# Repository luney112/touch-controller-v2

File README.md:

# touch-controller-v2

Version 2 of my touch controller for chunithm.

## TODO

- [ ] Finish firmware
- [ ] Test fully
- [ ] Write out docs and assembly instructions

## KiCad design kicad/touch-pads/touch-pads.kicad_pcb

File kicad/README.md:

# PCBs

There are two different PCB types: `mainboard` and `touch-pads`.

### mainboard

- Primary board everything connects to
- Only 1 copy of the board is required

### touch-pads

- Has the touch pads and LEDs
- 4 copies of the board is required

### development

- Use KiCad 9+
- Install the [espressif libraries](https://github.com/espressif/kicad-libraries)
- Install interactive html bom plugin

### manufacturing

- The `gerber.zip` files that are committed should be enough for manufacturing
- I use JlcPcb as they seem to offer the best prices for boards larger than 100mm x 100mm
- Suggested settings:
  - FR-4
  - 2 layers
  - At least 4 boards
  - 1.6mm thickness
  - Black color
  - HASL finish
  - 1 oz cu
  - Tented vias
  - 0.3mm min via hole size
  - Remove mark on PCB

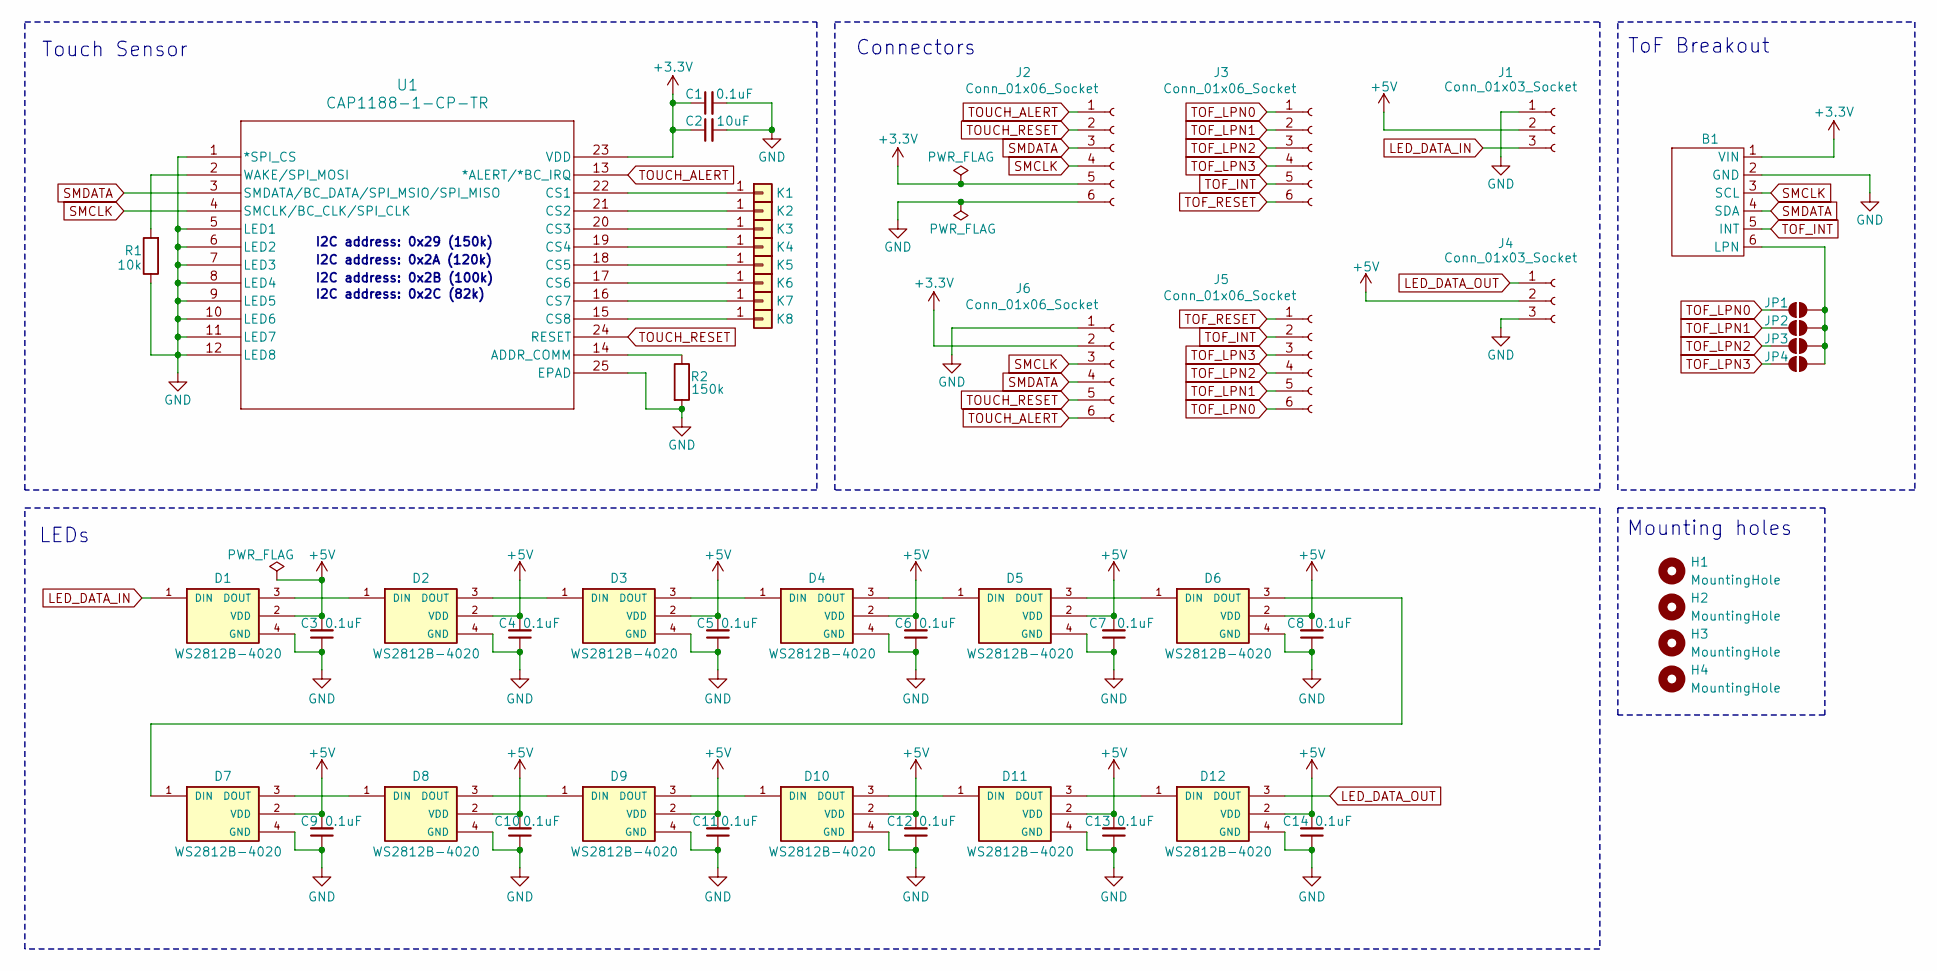
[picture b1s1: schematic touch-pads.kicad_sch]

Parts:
B1: VL53L5CX_Breakout_Aliexpress
C1, C3, C4, C5, C6, C7, C8, C9, C10, C11, C12, C13, C14: 0.1uF; C_0805_2012Metric_Pad1.18x1.45mm_HandSolder
C2: 10uF; C_0805_2012Metric_Pad1.18x1.45mm_HandSolder
D1, D2, D3, D4, D5, D6, D7, D8, D9, D10, D11, D12: WS2812B-4020; LED_WS2812B-4020; PARTREV V1.2
H1, H2, H3, H4: MountingHole; MountingHole_3.2mm_M3
J1, J4: Conn_01x03_Socket; JST_PH_S3B-PH-SM4-TB_1x03-1MP_P2.00mm_Horizontal
J2, J3, J5, J6: Conn_01x06_Socket; JST_GH_SM06B-GHS-TB_1x06-1MP_P1.25mm_Horizontal
JP1, JP2, JP3, JP4: SolderJumper_2_Open; SolderJumper-2_P1.3mm_Open_RoundedPad1.0x1.5mm
K1, K2, K3, K4, K5, K6, K7, K8: Conn_01x01; TouchKey_Standard
R1: 10k; R_0805_2012Metric_Pad1.20x1.40mm_HandSolder
R2: 150k; R_0805_2012Metric_Pad1.20x1.40mm_HandSolder
U1: CAP1188-1-CP-TR; QFN24_4X4MC_MCH

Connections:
+3.3V: B1.1 (VIN), C1.1, C2.1, J2.5, J6.2, U1.23 (VDD)
+5V: C3.2, C4.2, C5.2, C6.2, C7.2, C8.2, C9.2, C10.2, C11.2, C12.2, C13.2, C14.2, D1.2 (VDD), D2.2 (VDD), D3.2 (VDD), D4.2 (VDD), D5.2 (VDD), D6.2 (VDD), D7.2 (VDD), D8.2 (VDD), D9.2 (VDD), D10.2 (VDD), D11.2 (VDD), D12.2 (VDD), J1.2, J4.2
GND: B1.2 (GND), C1.2, C2.2, C3.1, C4.1, C5.1, C6.1, C7.1, C8.1, C9.1, C10.1, C11.1, C12.1, C13.1, C14.1, D1.4 (GND), D2.4 (GND), D3.4 (GND), D4.4 (GND), D5.4 (GND), D6.4 (GND), D7.4 (GND), D8.4 (GND), D9.4 (GND), D10.4 (GND), D11.4 (GND), D12.4 (GND), J1.1, J2.6, J4.3, J6.1, R1.1, R2.2, U1.1 (*SPI_CS), U1.5 (LED1), U1.6 (LED2), U1.7 (LED3), U1.8 (LED4), U1.9 (LED5), U1.10 (LED6), U1.11 (LED7), U1.12 (LED8), U1.25 (EPAD)
LED_DATA_IN: D1.1 (DIN), J1.3
LED_DATA_OUT: D12.3 (DOUT), J4.1
unnamed: B1.6 (LPN), JP1.2 (B), JP2.2 (B), JP3.2 (B), JP4.2 (B)
unnamed: D1.3 (DOUT), D2.1 (DIN)
unnamed: D2.3 (DOUT), D3.1 (DIN)
unnamed: D3.3 (DOUT), D4.1 (DIN)
unnamed: D4.3 (DOUT), D5.1 (DIN)
unnamed: D5.3 (DOUT), D6.1 (DIN)
unnamed: D6.3 (DOUT), D7.1 (DIN)
unnamed: D7.3 (DOUT), D8.1 (DIN)
unnamed: D8.3 (DOUT), D9.1 (DIN)
unnamed: D9.3 (DOUT), D10.1 (DIN)
unnamed: D10.3 (DOUT), D11.1 (DIN)
unnamed: D11.3 (DOUT), D12.1 (DIN)
unnamed: K1.1, U1.22 (CS1)
unnamed: K2.1, U1.21 (CS2)
unnamed: K3.1, U1.20 (CS3)
unnamed: K4.1, U1.19 (CS4)
unnamed: K5.1, U1.18 (CS5)
unnamed: K6.1, U1.17 (CS6)
unnamed: K7.1, U1.16 (CS7)
unnamed: K8.1, U1.15 (CS8)
unnamed: R2.1, U1.14 (ADDR_COMM)
unnamed: R1.2, U1.2 (WAKE/SPI_MOSI)
SMCLK: B1.3 (SCL), J2.4, J6.3, U1.4 (SMCLK/BC_CLK/SPI_CLK)
SMDATA: B1.4 (SDA), J2.3, J6.4, U1.3 (SMDATA/BC_DATA/SPI_MSIO/SPI_MISO)
TOF_INT: B1.5 (INT), J3.5, J5.2
TOF_LPN0: J3.1, J5.6, JP1.1 (A)
TOF_LPN1: J3.2, J5.5, JP2.1 (A)
TOF_LPN2: J3.3, J5.4, JP3.1 (A)
TOF_LPN3: J3.4, J5.3, JP4.1 (A)
TOF_RESET: J3.6, J5.1
TOUCH_ALERT: J2.1, J6.6, U1.13 (*ALERT/*BC_IRQ)
TOUCH_RESET: J2.2, J6.5, U1.24 (RESET)

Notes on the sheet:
ToF Breakout
I2C address: 0x2B (100k)
I2C address: 0x29 (150k)
LEDs
Mounting holes
Touch Sensor
Connectors
I2C address: 0x2C (82k)
I2C address: 0x2A (120k)

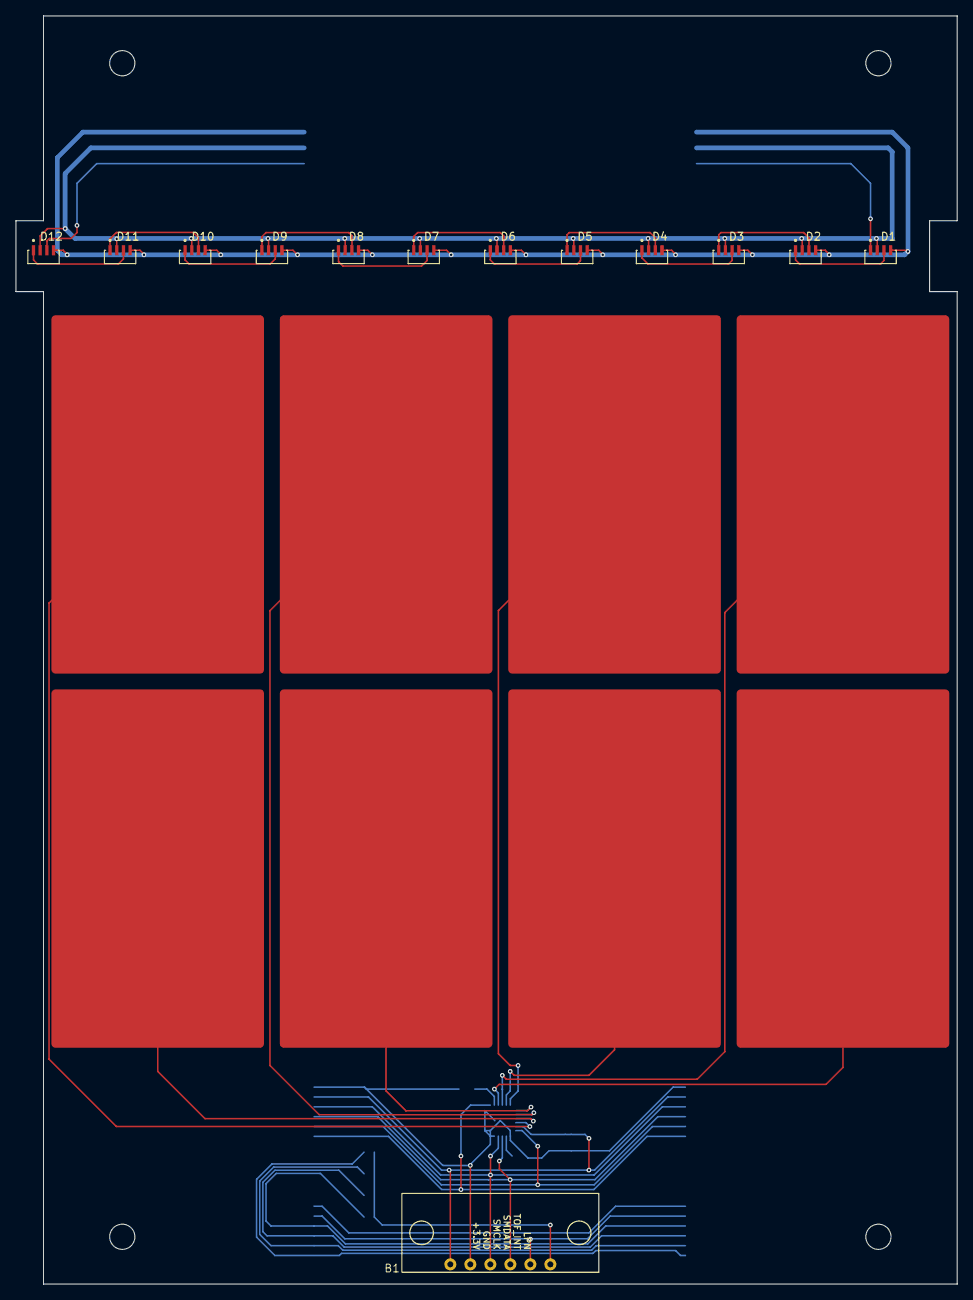
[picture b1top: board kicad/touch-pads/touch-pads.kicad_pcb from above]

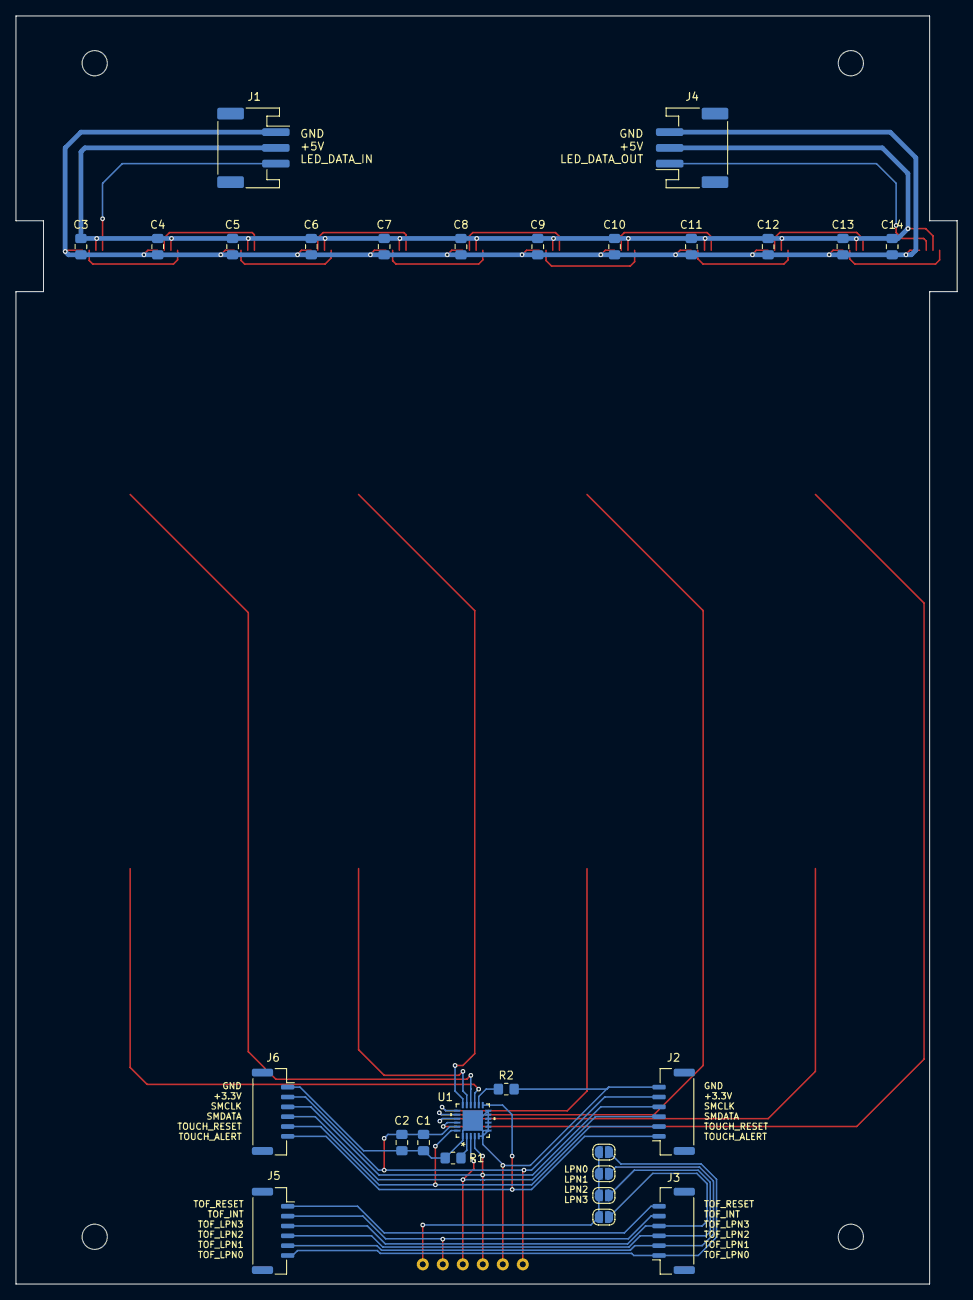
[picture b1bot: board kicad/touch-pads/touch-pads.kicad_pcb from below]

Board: 2 copper layers, 119.5 x 161.0 mm, 52 parts (27 on the bottom side), 37 nets.

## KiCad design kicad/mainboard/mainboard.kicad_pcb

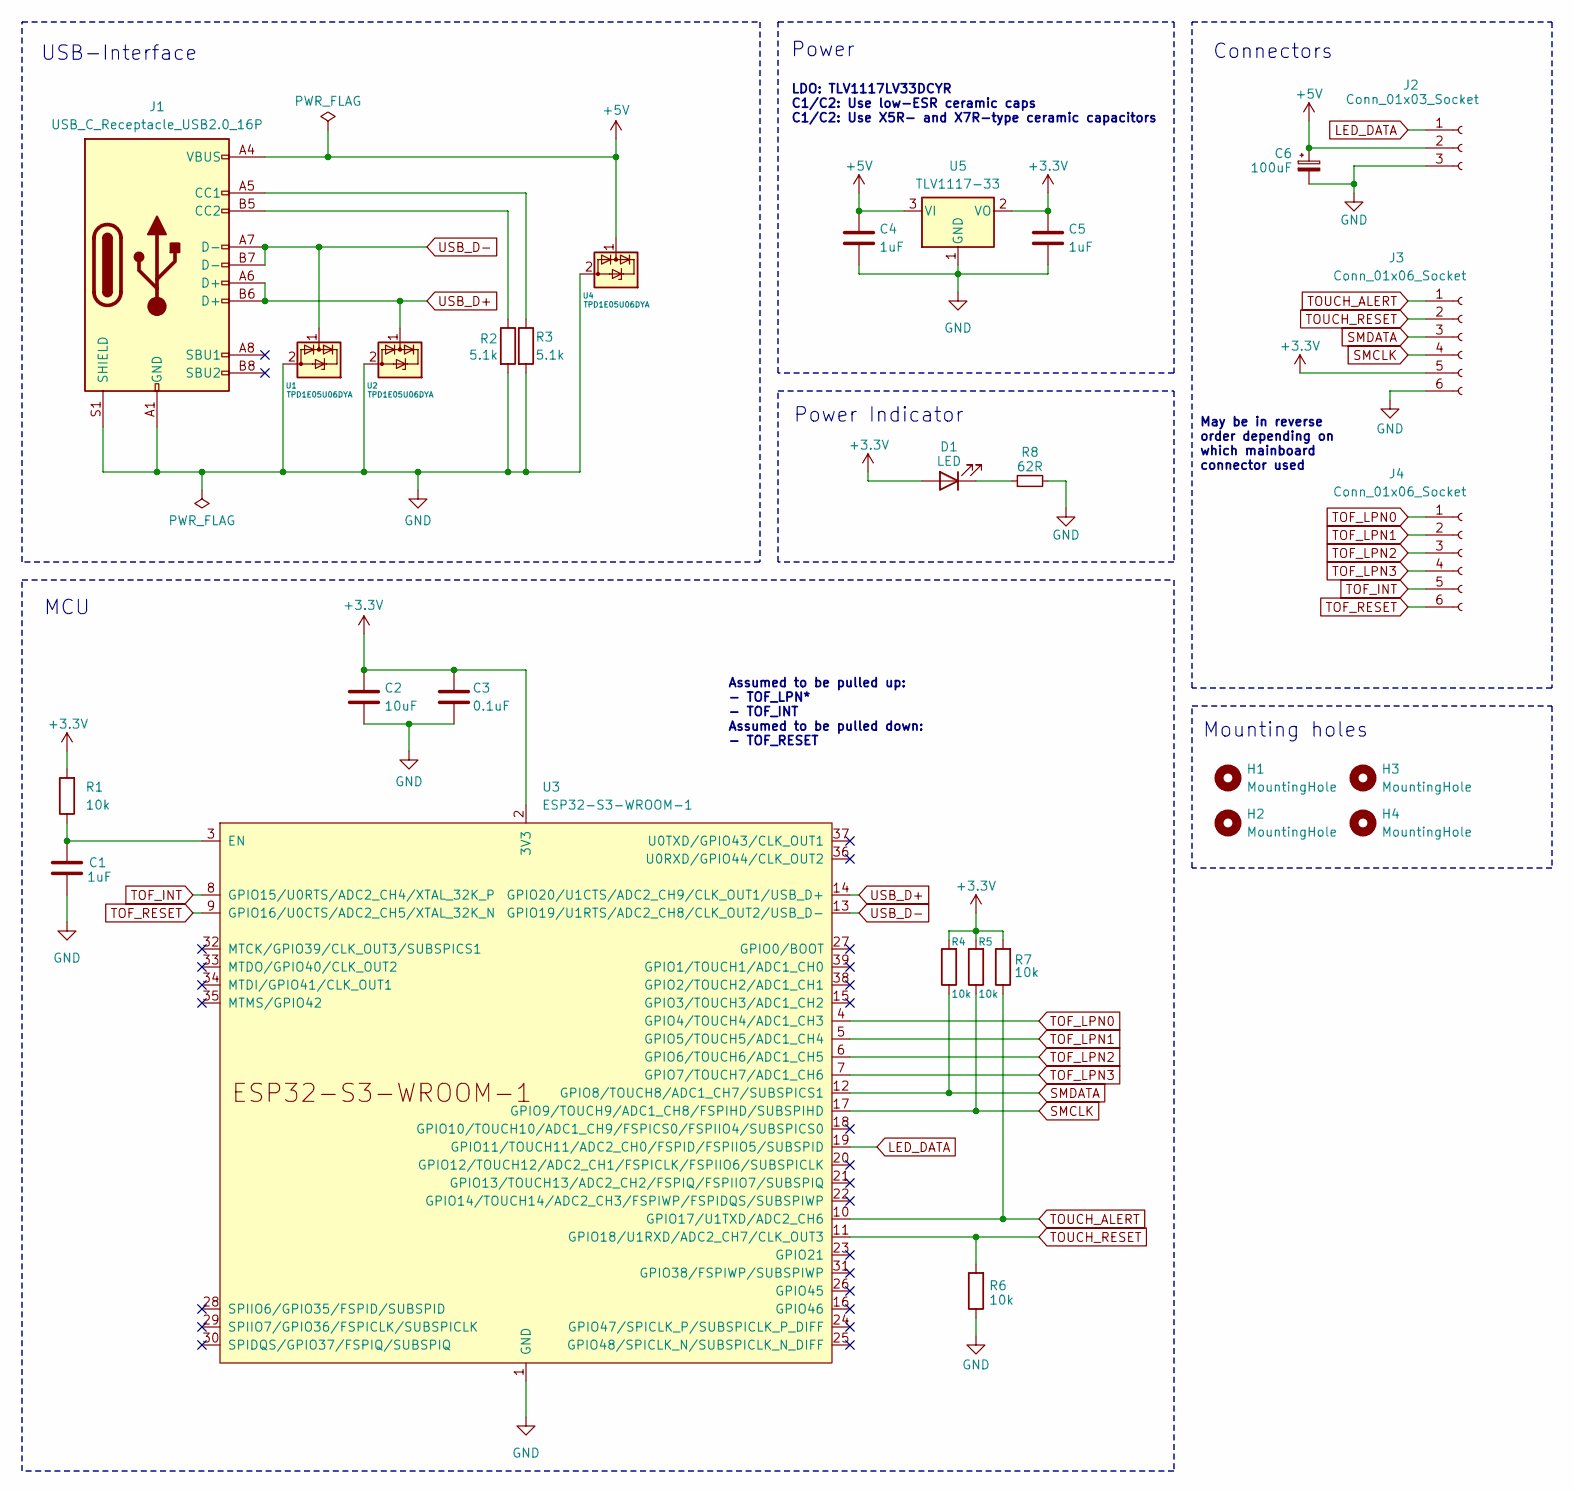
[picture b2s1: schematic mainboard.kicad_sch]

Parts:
C1, C4, C5: 1uF; C_0805_2012Metric_Pad1.18x1.45mm_HandSolder
C2: 10uF; C_0805_2012Metric_Pad1.18x1.45mm_HandSolder
C3: 0.1uF; C_0805_2012Metric_Pad1.18x1.45mm_HandSolder
C6: 100uF; CP_Elec_6.3x5.8
D1: LED; LED_0805_2012Metric_Pad1.15x1.40mm_HandSolder
H1, H2, H3, H4: MountingHole; MountingHole_2.2mm_M2
J1: USB_C_Receptacle_USB2.0_16P; USB_C_Receptacle_GCT_USB4105-xx-A_16P_TopMnt_Horizontal
J2: Conn_01x03_Socket; JST_PH_S3B-PH-SM4-TB_1x03-1MP_P2.00mm_Horizontal
J3, J4: Conn_01x06_Socket; JST_GH_SM06B-GHS-TB_1x06-1MP_P1.25mm_Horizontal
R1, R4, R5, R6, R7: 10k; R_0805_2012Metric_Pad1.20x1.40mm_HandSolder
R2, R3: 5.1k; R_0805_2012Metric_Pad1.20x1.40mm_HandSolder
R8: 62R; R_0805_2012Metric_Pad1.20x1.40mm_HandSolder
U1, U2, U4: TPD1E05U06DYA; D_SOD-523
U3: ESP32-S3-WROOM-1
U5: TLV1117-33; SOT-223-3_TabPin2

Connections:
+3.3V: C2.2, C3.2, C5.1, D1.2 (A), J3.5, R1.2, R4.2, R5.2, R7.2, U3.2 (3V3), U5.2 (VO)
+5V: C4.1, C6.1, J1.A4 (VBUS), J1.A9 (VBUS), J1.B4 (VBUS), J1.B9 (VBUS), J2.2, U4.1 (I/O), U5.3 (VI)
GND: C1.2, C2.1, C3.1, C4.2, C5.2, C6.2, J1.A1 (GND), J1.A12 (GND), J1.B1 (GND), J1.B12 (GND), J1.S1 (SHIELD), J2.3, J3.6, R2.2, R3.2, R6.1, R8.2, U1.2 (GND), U2.2 (GND), U3.1 (GND), U3.40 (GND), U3.41 (GND), U4.2 (GND), U5.1 (GND)
LED_DATA: J2.1, U3.19 (GPIO11/TOUCH11/ADC2_CH0/FSPID/FSPIIO5/S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)
unnamed: D1.1 (K), R8.1
unnamed: J1.A5 (CC1), R3.1
unnamed: J1.B5 (CC2), R2.1
unnamed: C1.1, R1.1, U3.3 (EN)
SMCLK: J3.4, R5.1, U3.17 (GPIO9/TOUCH9/ADC1_CH8/FSPIHD/SUBSPIHD)
SMDATA: J3.3, R4.1, U3.12 (GPIO8/TOUCH8/ADC1_CH7/SUBSPICS1)
TOF_INT: J4.5, U3.8 (GPIO15/U0RTS/ADC2_CH4/XTAL_32K_P)
TOF_LPN0: J4.1, U3.4 (GPIO4/TOUCH4/ADC1_CH3)
TOF_LPN1: J4.2, U3.5 (GPIO5/TOUCH5/ADC1_CH4)
TOF_LPN2: J4.3, U3.6 (GPIO6/TOUCH6/ADC1_CH5)
TOF_LPN3: J4.4, U3.7 (GPIO7/TOUCH7/ADC1_CH6)
TOF_RESET: J4.6, U3.9 (GPIO16/U0CTS/ADC2_CH5/XTAL_32K_N)
TOUCH_ALERT: J3.1, R7.1, U3.10 (GPIO17/U1TXD/ADC2_CH6)
TOUCH_RESET: J3.2, R6.2, U3.11 (GPIO18/U1RXD/ADC2_CH7/CLK_OUT3)
USB_D+: J1.A6 (D+), J1.B6 (D+), U2.1 (I/O), U3.14 (GPIO20/U1CTS/ADC2_CH9/CLK_OUT1/USB_D+)
USB_D-: J1.A7 (D-), J1.B7 (D-), U1.1 (I/O), U3.13 (GPIO19/U1RTS/ADC2_CH8/CLK_OUT2/USB_D-)

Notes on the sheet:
Assumed to be pulled up: - TOF_LPN* - TOF_INT Assumed to be pulled down: - TOF_RESET
May be in reverse order depending on which mainboard connector used
Power Indicator
Connectors
MCU
LDO: TLV1117LV33DCYR C1/C2: Use low-ESR ceramic caps C1/C2: Use X5R- and X7R-type ceramic capacitors
Mounting holes
USB-Interface
Power

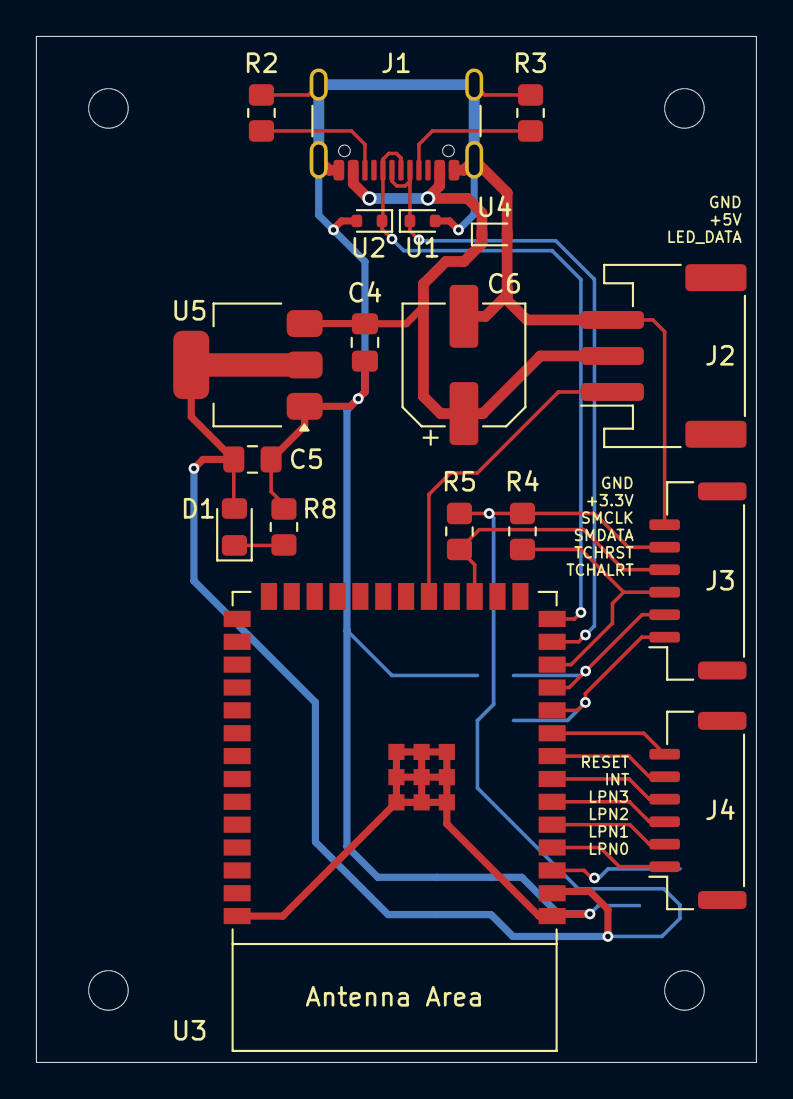
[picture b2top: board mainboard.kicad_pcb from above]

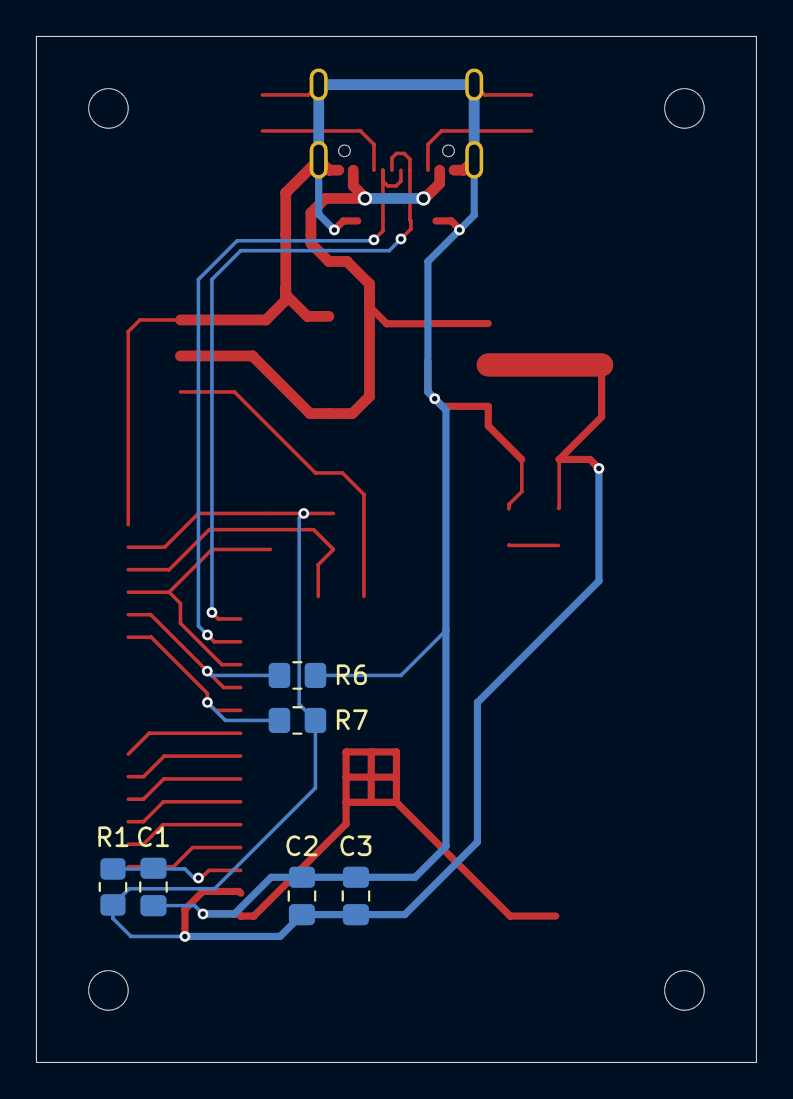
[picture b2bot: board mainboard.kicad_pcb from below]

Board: 2 copper layers, 40.0 x 57.0 mm, 28 parts (6 on the bottom side), 20 nets.

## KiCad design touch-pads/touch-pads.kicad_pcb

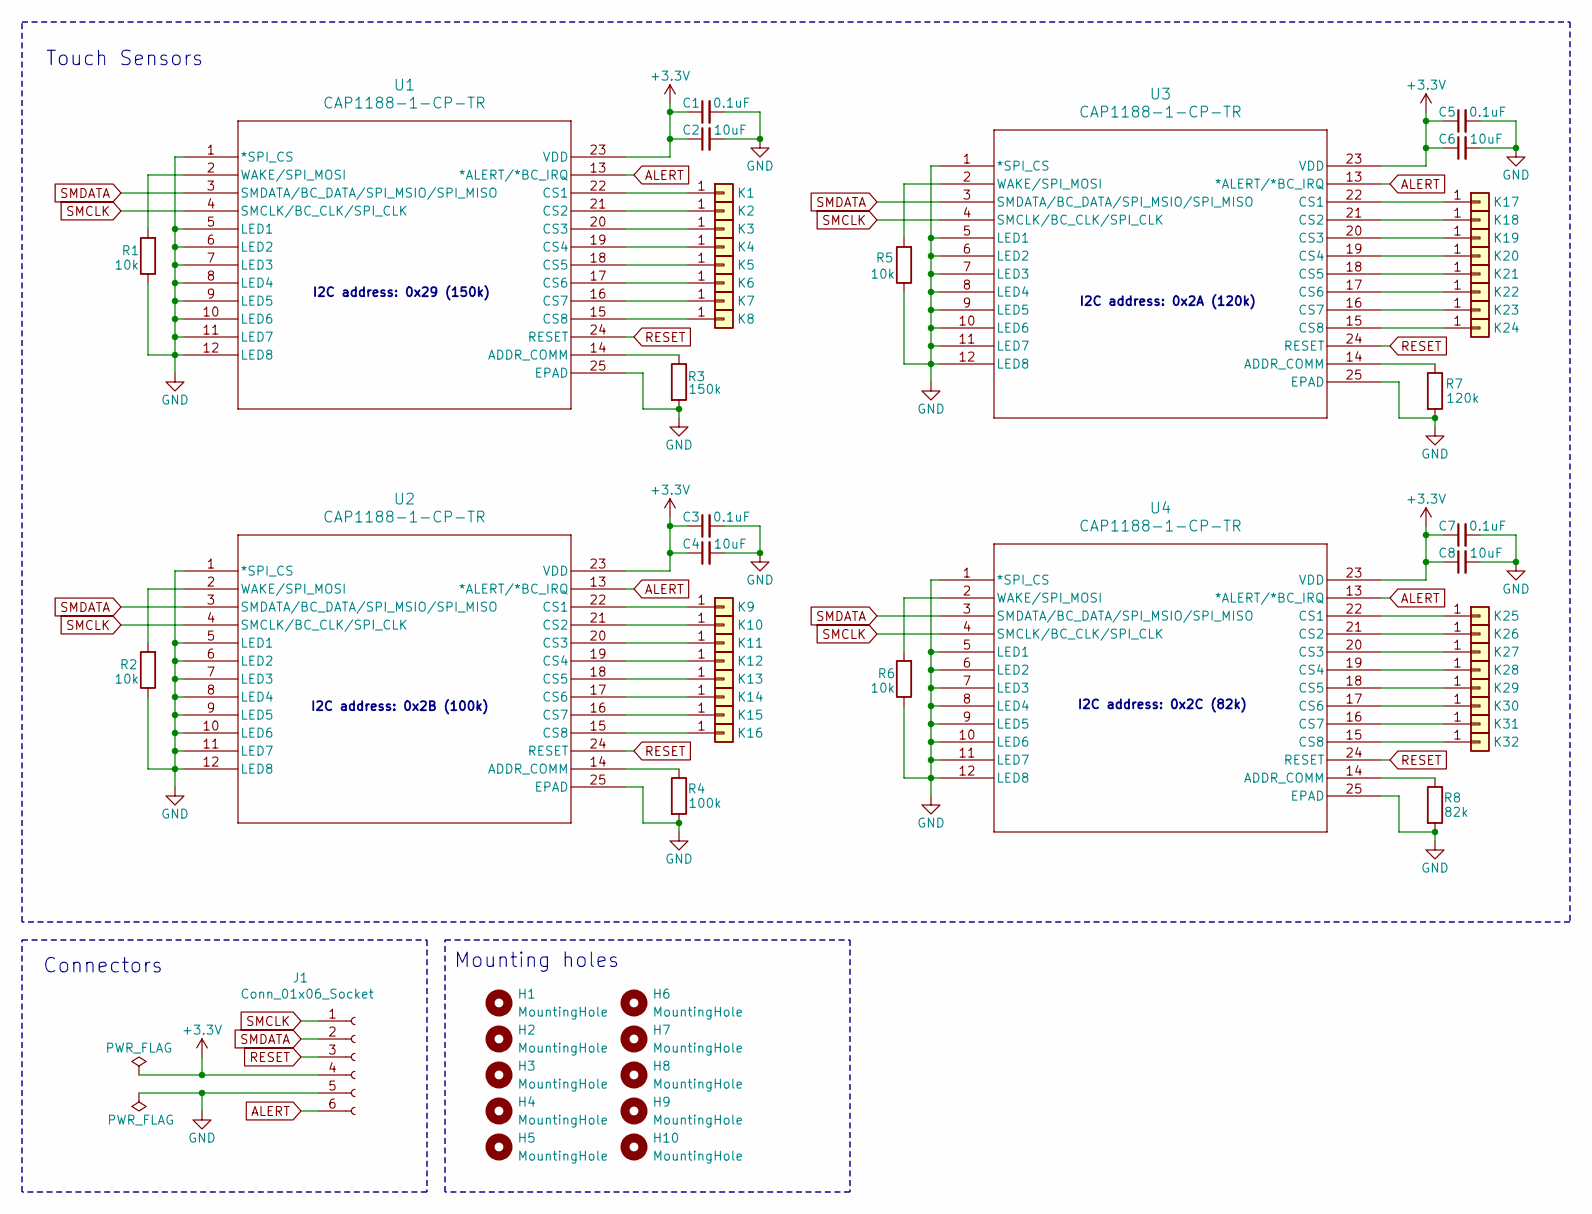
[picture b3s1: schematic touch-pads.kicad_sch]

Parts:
C1, C3, C5, C7: 0.1uF; C_0805_2012Metric_Pad1.18x1.45mm_HandSolder
C2, C4, C6, C8: 10uF; C_0805_2012Metric_Pad1.18x1.45mm_HandSolder
H1, H2, H3, H4, H5, H6, H7, H8, H9, H10: MountingHole; MountingHole_3.2mm_M3
J1: Conn_01x06_Socket; JST_XH_B6B-XH-A_1x06_P2.50mm_Vertical
K1, K2, K3, K4, K5, K6, K7, K8, K9, K10, K11, K12, K13, K14, K15, K16, K17, K18, K19, K20, K21, K22, K23, K24, K25, K26, K27, K28, K29, K30, K31, K32: Conn_01x01; TouchKey_Standard
R1, R2, R5, R6: 10k; R_0805_2012Metric_Pad1.20x1.40mm_HandSolder
R3: 150k; R_0805_2012Metric_Pad1.20x1.40mm_HandSolder
R4: 100k; R_0805_2012Metric_Pad1.20x1.40mm_HandSolder
R7: 120k; R_0805_2012Metric_Pad1.20x1.40mm_HandSolder
R8: 82k; R_0805_2012Metric_Pad1.20x1.40mm_HandSolder
U1, U2, U3, U4: CAP1188-1-CP-TR; QFN24_4X4MC_MCH

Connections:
+3.3V: C1.1, C2.1, C3.1, C4.1, C5.1, C6.1, C7.1, C8.1, J1.4, U1.23 (VDD), U2.23 (VDD), U3.23 (VDD), U4.23 (VDD)
ALERT: J1.6, U1.13 (*ALERT/*BC_IRQ), U2.13 (*ALERT/*BC_IRQ), U3.13 (*ALERT/*BC_IRQ), U4.13 (*ALERT/*BC_IRQ)
GND: C1.2, C2.2, C3.2, C4.2, C5.2, C6.2, C7.2, C8.2, J1.5, R1.1, R2.1, R3.2, R4.2, R5.1, R6.1, R7.2, R8.2, U1.1 (*SPI_CS), U1.5 (LED1), U1.6 (LED2), U1.7 (LED3), U1.8 (LED4), U1.9 (LED5), U1.10 (LED6), U1.11 (LED7), U1.12 (LED8), U1.25 (EPAD), U2.1 (*SPI_CS), U2.5 (LED1), U2.6 (LED2), U2.7 (LED3), U2.8 (LED4), U2.9 (LED5), U2.10 (LED6), U2.11 (LED7), U2.12 (LED8), U2.25 (EPAD), U3.1 (*SPI_CS), U3.5 (LED1), U3.6 (LED2), U3.7 (LED3), U3.8 (LED4), U3.9 (LED5), U3.10 (LED6), U3.11 (LED7), U3.12 (LED8), U3.25 (EPAD), U4.1 (*SPI_CS), U4.5 (LED1), U4.6 (LED2), U4.7 (LED3), U4.8 (LED4), U4.9 (LED5), U4.10 (LED6), U4.11 (LED7), U4.12 (LED8), U4.25 (EPAD)
unnamed: K1.1, U1.22 (CS1)
unnamed: K2.1, U1.21 (CS2)
unnamed: K3.1, U1.20 (CS3)
unnamed: K4.1, U1.19 (CS4)
unnamed: K5.1, U1.18 (CS5)
unnamed: K6.1, U1.17 (CS6)
unnamed: K7.1, U1.16 (CS7)
unnamed: K8.1, U1.15 (CS8)
unnamed: K9.1, U2.22 (CS1)
unnamed: K10.1, U2.21 (CS2)
unnamed: K11.1, U2.20 (CS3)
unnamed: K12.1, U2.19 (CS4)
unnamed: K13.1, U2.18 (CS5)
unnamed: K14.1, U2.17 (CS6)
unnamed: K15.1, U2.16 (CS7)
unnamed: K16.1, U2.15 (CS8)
unnamed: K17.1, U3.22 (CS1)
unnamed: K18.1, U3.21 (CS2)
unnamed: K19.1, U3.20 (CS3)
unnamed: K20.1, U3.19 (CS4)
unnamed: K21.1, U3.18 (CS5)
unnamed: K22.1, U3.17 (CS6)
unnamed: K23.1, U3.16 (CS7)
unnamed: K24.1, U3.15 (CS8)
unnamed: K25.1, U4.22 (CS1)
unnamed: K26.1, U4.21 (CS2)
unnamed: K27.1, U4.20 (CS3)
unnamed: K28.1, U4.19 (CS4)
unnamed: K29.1, U4.18 (CS5)
unnamed: K30.1, U4.17 (CS6)
unnamed: K31.1, U4.16 (CS7)
unnamed: K32.1, U4.15 (CS8)
unnamed: R3.1, U1.14 (ADDR_COMM)
unnamed: R1.2, U1.2 (WAKE/SPI_MOSI)
unnamed: R4.1, U2.14 (ADDR_COMM)
unnamed: R2.2, U2.2 (WAKE/SPI_MOSI)
unnamed: R7.1, U3.14 (ADDR_COMM)
unnamed: R5.2, U3.2 (WAKE/SPI_MOSI)
unnamed: R8.1, U4.14 (ADDR_COMM)
unnamed: R6.2, U4.2 (WAKE/SPI_MOSI)
RESET: J1.3, U1.24 (RESET), U2.24 (RESET), U3.24 (RESET), U4.24 (RESET)
SMCLK: J1.1, U1.4 (SMCLK/BC_CLK/SPI_CLK), U2.4 (SMCLK/BC_CLK/SPI_CLK), U3.4 (SMCLK/BC_CLK/SPI_CLK), U4.4 (SMCLK/BC_CLK/SPI_CLK)
SMDATA: J1.2, U1.3 (SMDATA/BC_DATA/SPI_MSIO/SPI_MISO), U2.3 (SMDATA/BC_DATA/SPI_MSIO/SPI_MISO), U3.3 (SMDATA/BC_DATA/SPI_MSIO/SPI_MISO), U4.3 (SMDATA/BC_DATA/SPI_MSIO/SPI_MISO)

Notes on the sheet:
I2C address: 0x2B (100k)
I2C address: 0x29 (150k)
Mounting holes
Touch Sensors
Connectors
I2C address: 0x2C (82k)
I2C address: 0x2A (120k)

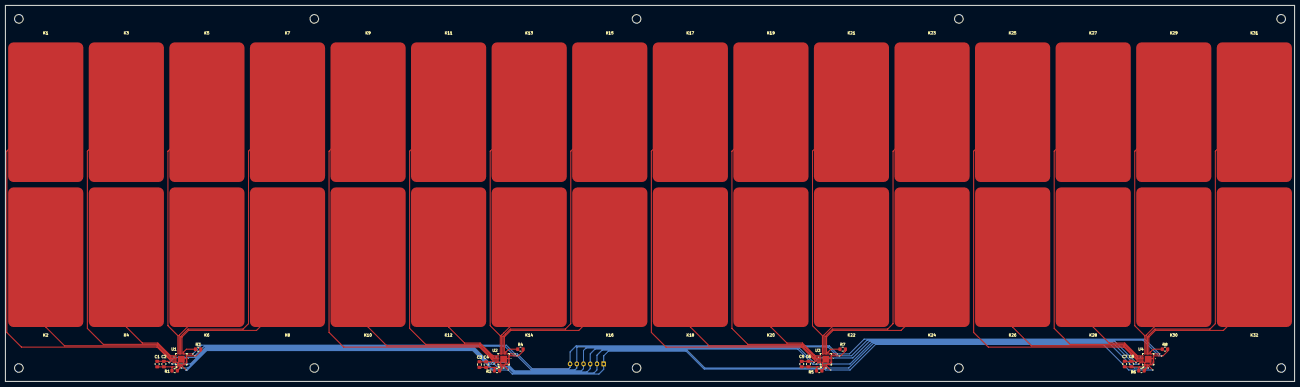
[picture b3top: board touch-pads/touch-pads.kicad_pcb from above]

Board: 2 copper layers, 480.0 x 140.0 mm, 63 parts (1 on the bottom side), 46 nets.

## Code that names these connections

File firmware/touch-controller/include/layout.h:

#ifndef LAYOUT_H
#define LAYOUT_H

// ---------------------------------------------------------
//                  View from the front/top
// ---------------------------------------------------------
//                    Touch sensor layout
// ---------------------------------------------------------
// |      0      |      1      |      2      |      3      |
// ---------------------------------------------------------
// |    0x2C     |    0x2B     |    0x2A     |    0x29     |
// ---------------------------------------------------------
// | 01 03 05 07 | 01 03 05 07 | 01 03 05 07 | 01 03 05 07 |
// | 02 04 06 08 | 02 04 06 08 | 02 04 06 08 | 02 04 06 08 |
//----------------------------------------------------------
// | 01 03 05 07 | 09 11 13 15 | 17 19 21 23 | 25 27 29 31 |
// | 02 04 06 08 | 10 12 14 16 | 18 20 22 24 | 26 28 30 32 |
// ---------------------------------------------------------
//                        ToF sensors
// ---------------------------------------------------------
// |      0      |      1      |      2      |      3      |
// ---------------------------------------------------------
// |    0x2D     |    0x2E     |    0x2F     |    0x30     |
// ---------------------------------------------------------

// Direction is relative to the front/top of the board
// Leftmost = Key0, Rightmost = Key15
enum LedDirection { LeftToRight = 0, RightToLeft = 1 };

// 0x2C->82k | 0x2B->100k | 0x2A->120k | 0x29->150k
// These are 7-bit addresses
#define CAP1188_ADDR_0 0x2C
#define CAP1188_ADDR_1 0x2B
#define CAP1188_ADDR_2 0x2A
#define CAP1188_ADDR_3 0x29

// These addresses are assigned dynamically at runtime
// These are 7-bit addresses
#define TOF_ADDR_0 0x2D
#define TOF_ADDR_1 0x2E
#define TOF_ADDR_2 0x2F
#define TOF_ADDR_3 0x30

#define LED_OFFSET 0         // Offset from the first LED
#define LED_SEGMENT_COUNT 47 // 16 keys (x2) and 15 dividers
#define LED_COUNT (LED_OFFSET + LED_SEGMENT_COUNT)
#define LED_DIRECTION RightToLeft // 0 = left->right, 1 = right->left

// --- Pins ---

#define GPIO_TOF_LPN0 4
#define GPIO_TOF_LPN1 5
#define GPIO_TOF_LPN2 6
#define GPIO_TOF_LPN3 7
#define GPIO_TOF_INT 15
#define GPIO_TOF_RESET 16

#define GPIO_I2C_SDA 8
#define GPIO_I2C_SCL 9

#define GPIO_TOUCH_ALERT 17
#define GPIO_TOUCH_RESET 18

#define GPIO_LED_DATA 11

#endif

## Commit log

2024-12-03 small board
2024-12-04 large board
2024-12-04 more work
2024-12-04 add bypass caps
2024-12-04 gerber
2024-12-04 move out gitfiles
2024-12-04 mounting holes on schematic
2024-12-04 split version
2024-12-05 tweaks to split
2024-12-05 angled jst
2024-12-05 add variant resistors
2024-12-05 add ibom
2024-12-05 update refs and tracks
2024-12-05 align between two pcbs
2024-12-05 adjust text
2024-12-05 organize files
2024-12-05 bom, update readme, move connector
2024-12-06 mainboard v1
2024-12-06 remove junk READMEs
2024-12-06 mainboard pcb v1
2024-12-07 mainboard cleaned
2024-12-08 more cleanup
2024-12-08 via/trace cleanup, larger via for 5v2a
2024-12-08 adjust edge cut
2024-12-08 Add logo
2024-12-08 fix erc
2024-12-08 add mountholes
2024-12-08 solder mask logo
2024-12-09 drc exl
2024-12-09 remove buttons
2024-12-09 move common lib, cleanup tracks, logo
2024-12-10 update gitignores
2024-12-11 init firmware
2024-12-13 Adjust layout
2024-12-13 update led
2024-12-27 Add some lasercut files stuff
2025-01-05 fix board connectivity
2025-01-06 v1 cap testing
2025-01-20 remove full-board version
2025-01-21 remove switches
2025-01-21 remove switch lib, add label for led connectors
2025-01-21 rename touch-pads-split to touch-pads
2025-01-22 update touch pad
2025-01-22 remove unncessary lib elements
2025-01-22 fix some 3d models
2025-01-23 fixup stuff
2025-01-23 mainboard gerber
2025-01-23 touch-pad gerber
2025-01-23 fix label
2025-01-23 Add pcb readme
2025-01-23 some docs
2025-01-23 update lasercutting
2025-01-27 v1 controller cad
2025-02-05 fixes + bambu project
2025-02-06 fix led type
2025-02-07 support more caps
2025-03-12 air exp
2025-03-16 reverse touch addr
2025-03-16 fixes
2025-05-17 v3 mainboard with more tof sensors
2025-05-17 sync footprints or something
2025-05-18 v3 touchpads with Tof sensors
2025-05-18 cleanup some
2025-05-18 excl
2025-05-18 cap ordering
2025-05-18 code test
2025-05-18 update to kicad 9
2025-05-19 bom gerber readme
2025-05-20 code update
2025-05-20 tof tweaks
2025-05-21 comments
2025-05-25 refactor some stuff
2025-05-25 update deps, add missing ret
2025-05-26 add mount holes
2025-05-26 re-route mainboard for better connectors
2025-05-26 change led to 11
2025-05-26 adjust breakout board to be more accurate
2025-05-26 final tweaks
2025-05-27 route LDO after TVS
2025-05-27 fix breakout board
2025-05-27 gerber and bom
2025-05-27 fix some jlpcb complaints
2025-05-29 real final tweaks for now
2025-06-01 update lasercut
2025-06-14 update cad
2025-06-15 update bambu
2025-06-22 attempt air tuning
2025-06-24 more fixes
2025-06-25 led fixes
2025-06-25 add in chuniio code
2025-06-26 tweaks
2025-06-26 fix bugs
2025-06-26 Add more delays
2025-06-27 tuning
2025-06-27 fix serial read
2025-06-28 touch tuning
2025-06-28 led brightness to max
